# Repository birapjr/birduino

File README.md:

# birduino
Prototype board for common projects

Current version: 1.1

The PCB images:

3D view

Front

Back

Main features:

  * Microcontroller: ATMEGA328
  * Main voltage: 3.7 V
  * Radio card: nRF24L01
  * Sensor: Temperature DS18B20
  * Display: OLED
  * Buttons: 4
  * Setup output: 5V
  * Power controls: 3 MOSFET 2N7000
  * Analog reader: 1 pin at J9
  * Free pins: 2, D6 and D10
  * Programming: Onboard serial programming

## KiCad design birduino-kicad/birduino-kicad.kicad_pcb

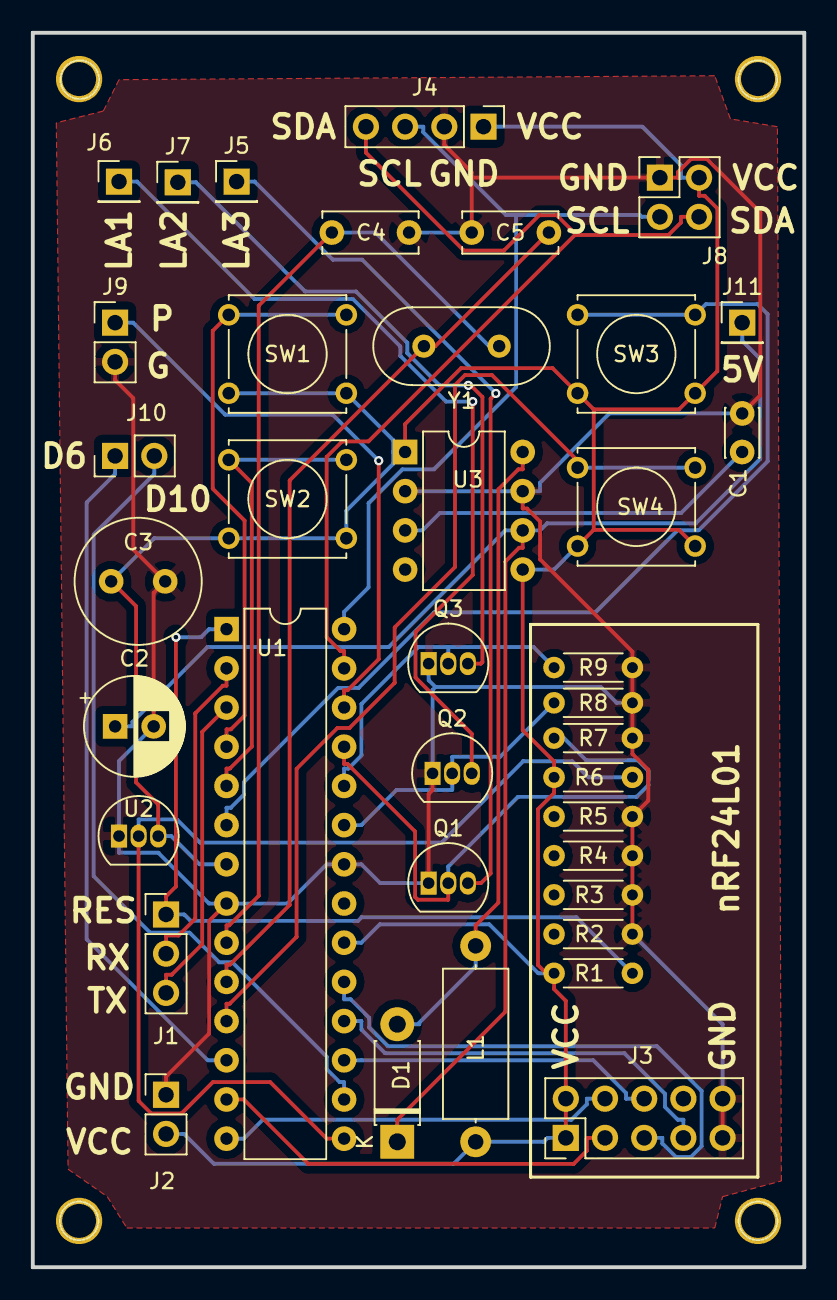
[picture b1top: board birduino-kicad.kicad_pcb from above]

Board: 2 copper layers, 50.0 x 80.0 mm, 38 parts (0 on the bottom side), 31 nets.

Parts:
C1: 0.1uF; C_Disc_D3.0mm_W2.0mm_P2.50mm
C2: 100uF; CP_Radial_D6.3mm_P2.50mm
C3: 150uF; C_Radial_D8.0mm_H7.0mm_P3.50mm
C4, C5: 22uF; C_Disc_D6.0mm_W2.5mm_P5.00mm
D1: 1N5817; D_DO-41_SOD81_P7.62mm_Horizontal
J1: Conn_01x03_Male; PinHeader_1x03_P2.54mm_Vertical
J2, J10: Conn_01x02_Male; PinHeader_1x02_P2.54mm_Vertical
J3: Conn_02x05_Odd_Even; PinHeader_2x05_P2.54mm_Vertical
J4: Conn_01x04; PinHeader_1x04_P2.54mm_Vertical
J5, J6, J7, J11: Conn_01x01_Male; PinHeader_1x01_P2.54mm_Vertical
J8: Conn_02x02_Odd_Even; PinHeader_2x02_P2.54mm_Vertical
J9: Conn_01x02; PinHeader_1x02_P2.54mm_Vertical
L1: 22uH; L_Axial_L9.5mm_D4.0mm_P12.70mm_Horizontal_Fastron_SMCC
Q1, Q2, Q3: 2N7000; TO-92_Inline
R1, R2, R3, R4, R5, R7, R8, R9: 10k; R_Axial_DIN0204_L3.6mm_D1.6mm_P5.08mm_Horizontal
R6: 4.7k; R_Axial_DIN0204_L3.6mm_D1.6mm_P5.08mm_Horizontal
SW1, SW2, SW3, SW4: SW_Push_Dual; SW_Tactile_Straight_KSA0Axx1LFTR
U1: ATMEGA328-PU; DIP-28_W7.62mm
U2: DS18B20; TO-92_Inline
U3: MAX756CPA; DIP-8_W7.62mm
Y1: Crystal; Crystal_HC49-4H_Vertical

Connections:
/StepUp5V/5V: C2.1, D1.1, J11.1, U3.6
BT1: SW1.1, U1.4
BT2: SW2.1, U1.5
BT3: SW3.1, U1.6
BT4: SW4.1, U1.11
CE: J3.3, U1.13
CSN: J3.4, U1.14
FREE: J10.1, U1.12
FREE2: J10.2, U1.16
GND: C1.2, C2.2, C3.2, C4.2, C5.1, J2.1, J3.9, J3.10, J4.2, J8.1, J9.2, Q1.1, Q2.1, Q3.1, R2.1, R3.1, R4.1, R5.1, R7.2, R8.2, R9.2, U1.8, U1.22, U2.1, U3.2, U3.7
LED1: Q2.2, R8.1, U1.23
LED2: Q3.2, R9.1, U1.24
LED3: Q1.2, R7.1, U1.25
MI: J3.7, U1.18
MO: J3.6, U1.17
unnamed: C1.1, U3.3
unnamed: D1.2, L1.2, U3.8
unnamed: J1.1, R1.1, U1.1
unnamed: J1.2, U1.2
unnamed: J1.3, U1.3
unnamed: J5.1, Q1.3
unnamed: J6.1, Q2.3
unnamed: J7.1, Q3.3
PUMP: J9.1, U1.26
SCK: J3.5, U1.19
SCL: J4.3, J8.3, U1.28
SDA: J4.4, J8.4, U1.27
TEMP: R6.1, U1.15, U2.2
VCC: C3.1, J2.2, J3.1, J3.2, J4.1, J8.2, L1.1, R1.2, R6.2, SW1.2, SW2.2, SW3.2, SW4.2, U1.7, U1.20, U2.3, U3.1, U3.5
XTAL1: C4.1, U1.9, Y1.1
XTAL2: C5.2, U1.10, Y1.2

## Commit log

2019-02-13 feat: Initial KiCad project
2019-02-19 feat: Added more components to the board
2019-02-25 feat: add radio card connections, added the first routing of vias, added backside label.
2019-02-27 feat: add 4 button to board
2019-03-04 feat: add footprint to the buttons, new routing with butons.
2019-03-05 feat: add display to board
2019-03-11 feat: migrate to Kicad 5, add LEDs control, add temperature sensor.
2019-03-25 feat: add new sensors and components
2019-04-07 feat: First final version 1.0. 3D image added to readme
2019-04-13 feat: added Crytal to PCB. Added new images to readme.
2019-04-13 fix: ajusted readme.
2019-04-14 feat: add fixation holes. First fabrication files. Version 1.0 closed for production.
2019-04-16 feat: Version 1.1. Better size, ground plat and proper fabrication files.
2019-04-16 feat: add fabrication.zip to .gitignore
2019-04-16 Update README.md
    Small fix.
2019-04-20 Update README.md
    fix: typo
2020-11-15 feat: remote-control under progress
